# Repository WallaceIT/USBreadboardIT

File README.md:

USBreadboardIT board files and test firmware+software

The firmware is based on [m-stack](https://github.com/signal11/m-stack) by signal11 and can be opened in MPLAB X and compiled with the XC8 compiler by Microchip.
Please note that the enclosed project is pre-configured with ROM settings to be used with the 512-words [DFU booloader](https://github.com/majbthrd/PIC16F1-USB-DFU-Bootloader) by majbthrd, but can easily be adapted to be uploaded through ICSP (just remove the 'ROM ranges' and 'Codeoffset' options).

The software, written in python, requires [PySide](https://github.com/PySide/PySide) and [cython-hidapi](https://github.com/trezor/cython-hidapi), both installable through pip either on Windows or Linux.

Work in progress, see the [hackaday.io page](https://hackaday.io/project/7921-usbreadboardit) for details

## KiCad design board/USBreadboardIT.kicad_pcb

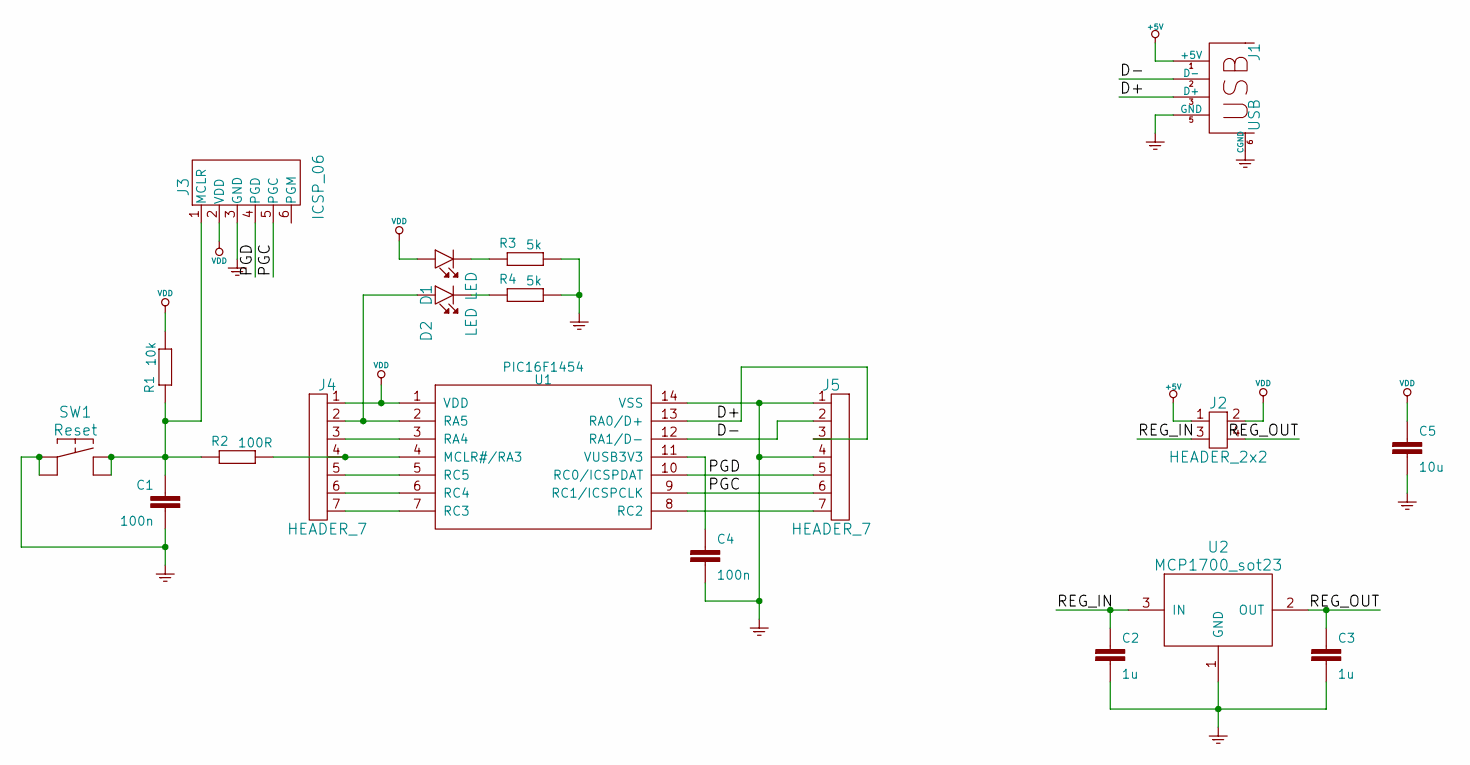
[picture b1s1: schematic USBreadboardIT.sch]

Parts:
C1, C4: 100n; C_0805
C2, C3: 1u; C_0805
C5: 10u; C_0805
D1, D2: LED; LED-0805
J1: USB; USB_Mini-B
J2: HEADER_2x2; Pin_Header_Straight_2x02
J3: ICSP_06; Pin_Header_Straight_1x06
J4, J5: HEADER_7; Pin_Header_Straight_1x07
R1: 10k; R_0805
R2: 100R; R_0805
R3, R4: 5k; R_0805
SW1: Reset; SW_SPST_PTS645
U1: PIC16F1454; SOIC-14_3.9x8.7mm_Pitch1.27mm
U2: MCP1700_sot23; SOT-23_Handsoldering

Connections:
+5V: J1.1 (+5V), J2.1
/D+: J1.3 (D+), J5.3, U1.13 (RA0/D+)
/D-: J1.2 (D-), J5.2, U1.12 (RA1/D-)
/PGC: J3.5 (PGC), J5.6, U1.9 (RC1/ICSPCLK)
/PGD: J3.4 (PGD), J5.5, U1.10 (RC0/ICSPDAT)
/REG_IN: C2.1, J2.3, U2.3 (IN)
/REG_OUT: C3.1, J2.4, U2.2 (OUT)
GND: C1.2, C2.2, C3.2, C4.2, C5.2, J1.5 (GND), J1.6 (CGND), J3.3 (GND), J5.1, J5.4, R3.2, R4.2, SW1.1, U1.14 (VSS), U2.1 (GND)
unnamed: C1.1, J3.1 (MCLR), R1.1, R2.1, SW1.2
unnamed: C4.1, U1.11 (VUSB3V3)
unnamed: D1.2, R3.1
unnamed: D2.1, J4.2, U1.2 (RA5)
unnamed: D2.2, R4.1
unnamed: J4.3, U1.3 (RA4)
unnamed: J4.4, R2.2, U1.4 (MCLR#/RA3)
unnamed: J4.5, U1.5 (RC5)
unnamed: J4.6, U1.6 (RC4)
unnamed: J4.7, U1.7 (RC3)
unnamed: J5.7, U1.8 (RC2)
VDD: C5.1, D1.1, J2.2, J3.2 (VDD), J4.1, R1.2, U1.1 (VDD)

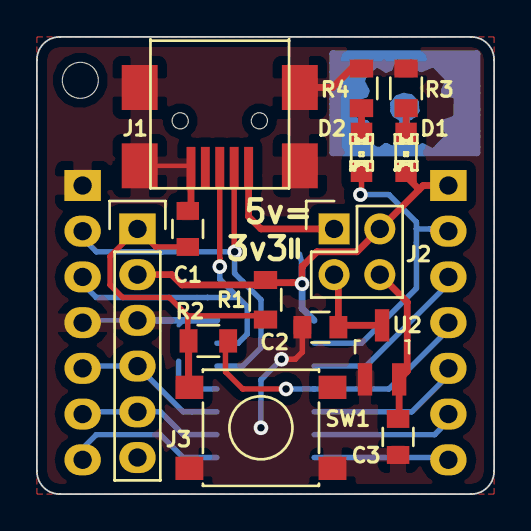
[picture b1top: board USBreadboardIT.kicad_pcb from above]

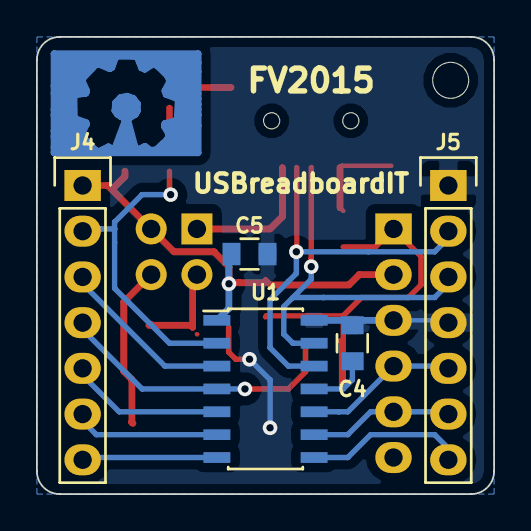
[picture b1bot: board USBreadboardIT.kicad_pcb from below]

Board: 2 copper layers, 25.4 x 25.4 mm, 20 parts (5 on the bottom side), 20 nets.

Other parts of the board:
HOLE: VAL**; HOLE

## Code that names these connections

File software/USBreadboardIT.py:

# -*- coding: utf-8 -*-

# Form implementation generated from reading ui file 'USBreadboardIT\usbreadboardit.ui'
#
# Created: Mon Oct 05 21:39:30 2015
#      by: pyside-uic 0.2.15 running on PySide 1.2.2
#
# WARNING! All changes made in this file will be lost!


import sys
import hid
from PySide import QtCore, QtGui
import time


class Display(QtGui.QWidget):
    def __init__(self, parent=None):
        super(Display, self).__init__(parent)

        hbox = QtGui.QHBoxLayout()
        grid_left = QtGui.QGridLayout()
        grid_right = QtGui.QGridLayout()

        self.red = QtGui.QPixmap("images/statusRed.png").scaled(QtCore.QSize(30, 30))
        self.green = QtGui.QPixmap("images/statusGreen.png").scaled(QtCore.QSize(30, 30))

        self.colors = [self.red, self.green]

        self.pins = ["GND1", "D-", "D+", "GND4", "RC0", "RC1", "RC2",
                     "RC3", "RC4", "RC5", "RA3", "RA4", "RA5", "VDD"]

        self.button_toggle = {'RC0': QtGui.QPushButton("TOGGLE"),
                              'RC1': QtGui.QPushButton("TOGGLE"),
                              'RC2': QtGui.QPushButton("TOGGLE"),
                              'RC3': QtGui.QPushButton("TOGGLE"),
                              'RC4': QtGui.QPushButton("TOGGLE"),
                              'RC5': QtGui.QPushButton("TOGGLE"),
                              'RA3': QtGui.QPushButton("TOGGLE"),
                              'RA4': QtGui.QPushButton("TOGGLE"),
                              'RA5': QtGui.QPushButton("TOGGLE")}

        self.button_pulse = {'RC0': QtGui.QPushButton("PULSE"),
                             'RC1': QtGui.QPushButton("PULSE"),
                             'RC2': QtGui.QPushButton("PULSE"),
                             'RC3': QtGui.QPushButton("PULSE"),
                             'RC4': QtGui.QPushButton("PULSE"),
                             'RC5': QtGui.QPushButton("PULSE"),
                             'RA3': QtGui.QPushButton("PULSE"),
                             'RA4': QtGui.QPushButton("PULSE"),
                             'RA5': QtGui.QPushButton("PULSE")}

        self.status = {'RC0': QtGui.QLabel(self),
                       'RC1': QtGui.QLabel(self),
                       'RC2': QtGui.QLabel(self),
                       'RC3': QtGui.QLabel(self),
                       'RC4': QtGui.QLabel(self),
                       'RC5': QtGui.QLabel(self),
                       'RA3': QtGui.QLabel(self),
                       'RA4': QtGui.QLabel(self),
                       'RA5': QtGui.QLabel(self),
                       'GND1': None, 'GND4': None, 'D-': None, 'D+': None, 'VDD': None}

        self.label = {'GND1': QtGui.QLabel("GROUND"),
                      'D-': QtGui.QLabel("D-"),
                      'D+': QtGui.QLabel("D+"),
                      'GND4': QtGui.QLabel("GROUND"),
                      'RC0': QtGui.QLabel("RC0"),
                      'RC1': QtGui.QLabel("RC1"),
                      'RC2': QtGui.QLabel("RC2"),
                      'RC3': QtGui.QLabel("RC3"),
                      'RC4': QtGui.QLabel("RC4"),
                      'RC5': QtGui.QLabel("RC5"),
                      'RA3': QtGui.QLabel("RA3"),
                      'RA4': QtGui.QLabel("RA4"),
                      'RA5': QtGui.QLabel("RA5"),
                      'VDD': QtGui.QLabel("VDD")}

        for key in self.label:
            self.label[key].setMinimumHeight(30)

        # #### LEFT GRID #### #

        grid_left.setRowStretch(0, 1)
        # Pin 1: GND
        for i in range(7):
            key = self.pins[i]
            j = i + 1
            if(self.status[key] is not None):
                grid_left.addWidget(self.button_pulse[key], j, 1)
                self.button_pulse[key].clicked.connect(lambda key=key: self.sendPulse(key))
                grid_left.addWidget(self.button_toggle[key], j, 2)
                self.button_toggle[key].clicked.connect(lambda key=key: self.sendToggle(key))
                grid_left.addWidget(self.label[key], j, 3)
                grid_left.addWidget(self.status[key], j, 4)
                self.status[key].setPixmap(self.red)
            else:
                grid_left.addWidget(self.label[key], j, 3, 1, 2)

        # #### CENTER IMAGE #### #
        vbox = QtGui.QVBoxLayout()
        QI = QtGui.QImage("images/board.png").scaled(QtCore.QSize(380, 380))
        boardImg = QtGui.QLabel(self)
        boardImg.setPixmap(QtGui.QPixmap.fromImage(QI))
        vbox.addStretch(1)
        vbox.addWidget(boardImg)

        # #### RIGHT GRID #### #
        grid_right.setRowStretch(0, 1)

        for i in range(7):
            key = self.pins[i + 7]
            j = 14 - i
            if(self.status[key] is not None):
                grid_right.addWidget(self.status[key], j, 1)
                self.status[key].setPixmap(self.red)
                grid_right.addWidget(self.label[key], j, 2)
                grid_right.addWidget(self.button_toggle[key], j, 3)
                self.button_toggle[key].clicked.connect(lambda key=key: self.sendToggle(key))
                grid_right.addWidget(self.button_pulse[key], j, 4)
                self.button_pulse[key].clicked.connect(lambda key=key: self.sendPulse(key))
            else:
                grid_right.addWidget(self.label[key], j, 1, 1, 4)

        hbox.addLayout(grid_left)
        hbox.addLayout(vbox)
        hbox.addLayout(grid_right)

        self.setLayout(hbox)

        self.setWindowTitle("USBreadboardIT")
        # -self.setWindowState(QtCore.Qt.WindowMaximized)

        self.offset = {'RC0': 30,
                       'RC1': 31,
                       'RC2': 32,
                       'RC3': 33,
                       'RC4': 34,
                       'RC5': 35,
                       'RA3': 13,
                       'RA4': 14,
                       'RA5': 15}

        self.g = hid.device()
        self.g.open(vendor_id=0xA0A0, product_id=0x0009)
        self.g.write([0x00, 0x02, 0x00, 0x00, 0x00])  # Set mode
        self.g.write([0x00, 0x03])  # Get value
        x = self.g.read(4)
        print(x)

        for i in range(14):
            key = self.pins[i]
            if self.status[key] is not None:
                status = (x[self.offset[key] / 10] >> (self.offset[key] % 10)) & 0x01
                self.status[key].setPixmap(self.colors[status])

    def __del__(self):
        self.g.close()

    @QtCore.Slot()
    def sendPulse(self, pin):
        print("PULSE on %s" % pin)
        self.g.write([0x00, 0x08, self.offset[pin], 0x01])
        time.sleep(0.2)
        self.g.write([0x00, 0x08, self.offset[pin], 0x00])

    @QtCore.Slot()
    def sendToggle(self, pin):
        print("TOGGLE on %s" % pin)
        self.g.write([0x00, 0x03])  # Get value
        x = self.g.read(4)
        status = (x[self.offset[pin] / 10] >> (self.offset[pin] % 10)) & 0x01

        if(status == 0x01):
            x[self.offset[pin] / 10] &= ~(0x01 << (self.offset[pin] % 10))
        else:
            x[self.offset[pin] / 10] |= (0x01 << (self.offset[pin] % 10))

        response = [0x00, 0x04, x[1], x[2], x[3]]
        self.g.write(response)  # Set mode

if __name__ == '__main__':

    app = QtGui.QApplication(sys.argv)
    clock = Display()
    clock.show()
    sys.exit(app.exec_())

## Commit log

2015-11-01 Firmware added. Software and README updated.
2015-12-18 Added pinout image
